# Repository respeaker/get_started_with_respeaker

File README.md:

## ReSpeaker Core V2 wiki

Now we have an new device, called **ReSpeaker Core V2**, with more powerful CPU, large eMMC and on-board 8channels microphone array.
Click here to [Getting started with ReSpeaker Core V2](/docs/ReSpeaker_Core_V2/README.md).

## ReSpeaker wiki

ReSpeaker is an open modular voice interface to hack things around you. Let you interact with your home appliances, your plant, your office, your internet-equipped devices or any other things in your daily life, all by your voice. Click here to [Getting Started with ReSpeaker](/docs/ReSpeaker/README.md).

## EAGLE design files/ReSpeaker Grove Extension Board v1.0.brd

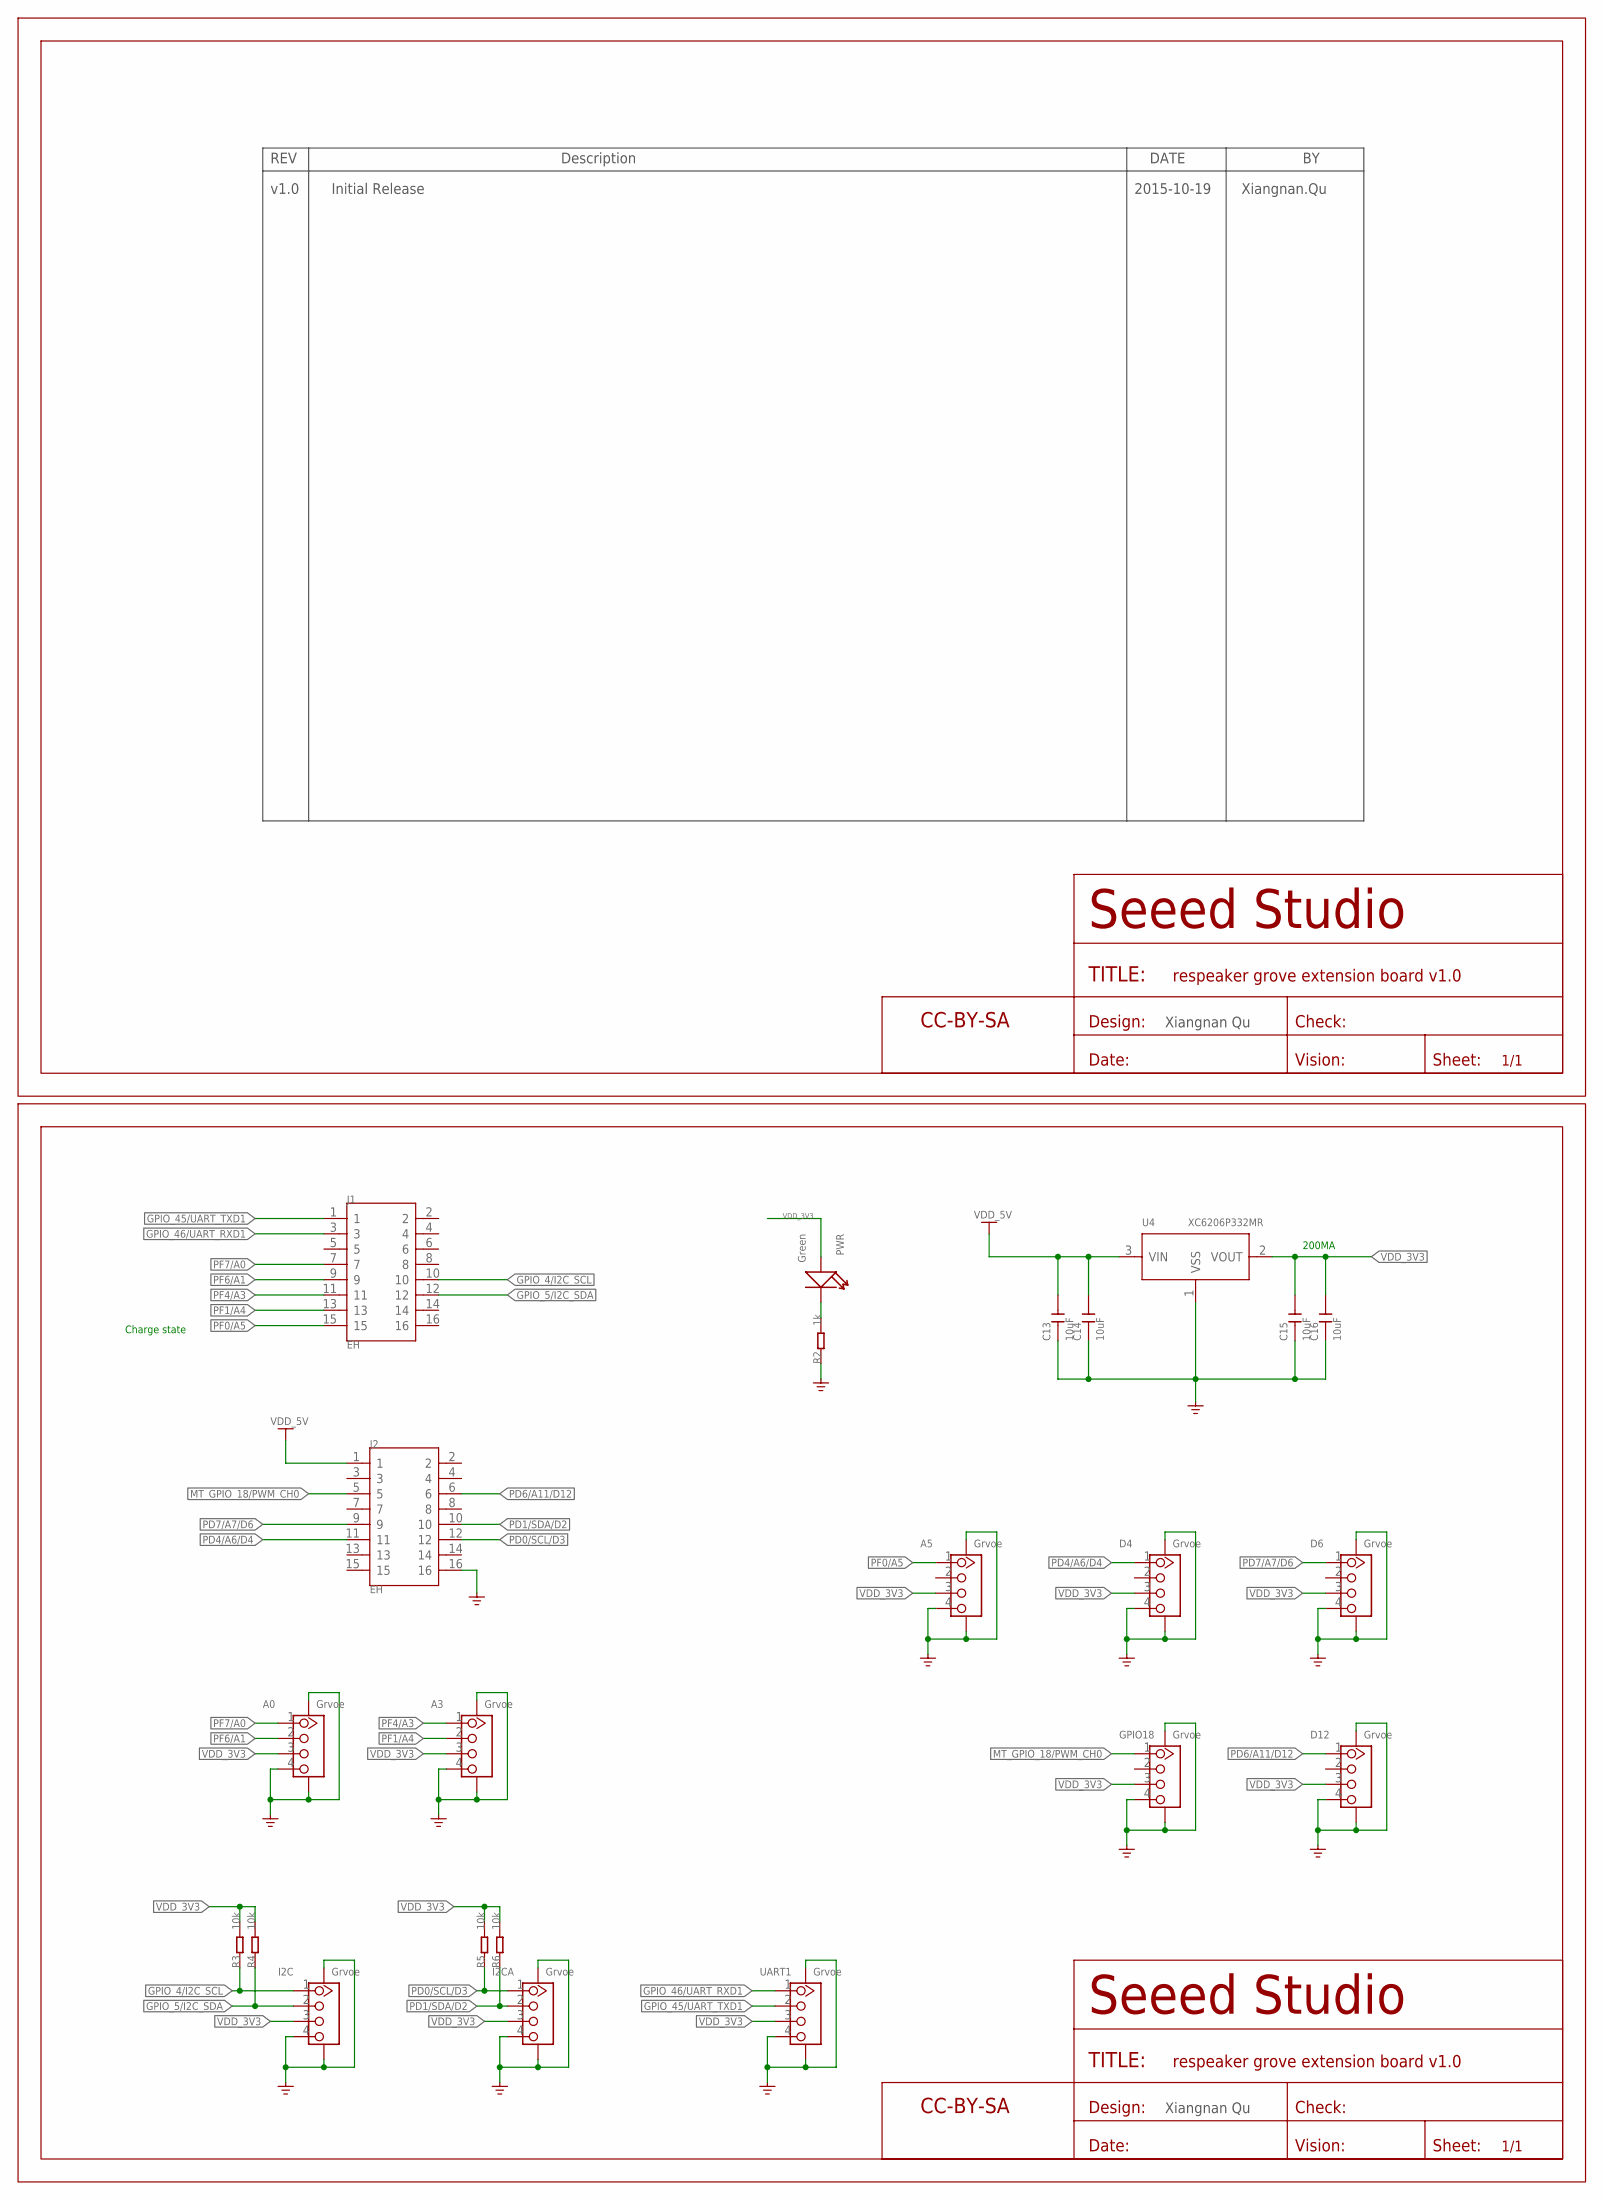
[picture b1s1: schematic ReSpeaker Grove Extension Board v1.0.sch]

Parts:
A0, A3, A5: Grvoe; HW4-SMD-2.0-90D
C13, C14, C15, C16: 10uF; C0603
D4, D6, D12: Grvoe; HW4-SMD-2.0-90D
FR1, FR2: SEEEDSTUDIO-OPEN-SCH-FRAME; SEEEDSTUDIO-PCB-FRAME
GPIO18: Grvoe; HW4-SMD-2.0-90D
I2C, I2CA: Grvoe; HW4-SMD-2.0-90D
J1, J2: EH; H2X8-2.0
PWR: Green; LED-0402
R2: 1k; R0402
R3, R4, R5, R6: 10k; R0402
U4: XC6206P332MR; SOT-23
UART1: Grvoe; HW4-SMD-2.0-90D

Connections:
GND: A0.4, A0.SS1, A0.SS2, A3.4, A3.SS1, A3.SS2, A5.4, A5.SS1, A5.SS2, C13.1, C14.1, C15.1, C16.1, D4.4, D4.SS1, D4.SS2, D6.4, D6.SS1, D6.SS2, D12.4, D12.SS1, D12.SS2, GPIO18.4, GPIO18.SS1, GPIO18.SS2, I2C.4, I2C.SS1, I2C.SS2, I2CA.4, I2CA.SS1, I2CA.SS2, J2.16, R2.1, U4.1 (VSS), UART1.4, UART1.SS1, UART1.SS2
GPIO_4/I2C_SCL: I2C.1, J1.10, R3.1
GPIO_5/I2C_SDA: I2C.2, J1.12, R4.1
GPIO_45/UART_TXD1: J1.1, UART1.2
GPIO_46/UART_RXD1: J1.3, UART1.1
MT_GPIO_18/PWM_CH0: GPIO18.1, J2.5
unnamed: PWR.-, R2.2
PD0/SCL/D3: I2CA.1, J2.12, R5.1
PD1/SDA/D2: I2CA.2, J2.10, R6.1
PD4/A6/D4: D4.1, J2.11
PD6/A11/D12: D12.1, J2.6
PD7/A7/D6: D6.1, J2.9
PF0/A5: A5.1, J1.15
PF1/A4: A3.2, J1.13
PF4/A3: A3.1, J1.11
PF6/A1: A0.2, J1.9
PF7/A0: A0.1, J1.7
VDD_3V3: A0.3, A3.3, A5.3, C15.2, C16.2, D4.3, D6.3, D12.3, GPIO18.3, I2C.3, I2CA.3, PWR.+, R3.2, R4.2, R5.2, R6.2, U4.2 (VOUT), UART1.3
VDD_5V: C13.2, C14.2, J2.1, U4.3 (VIN)

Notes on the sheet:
Xiangnan Qu
Charge state
200MA
Initial Release
v1.0
2015-10-19
Xiangnan.Qu

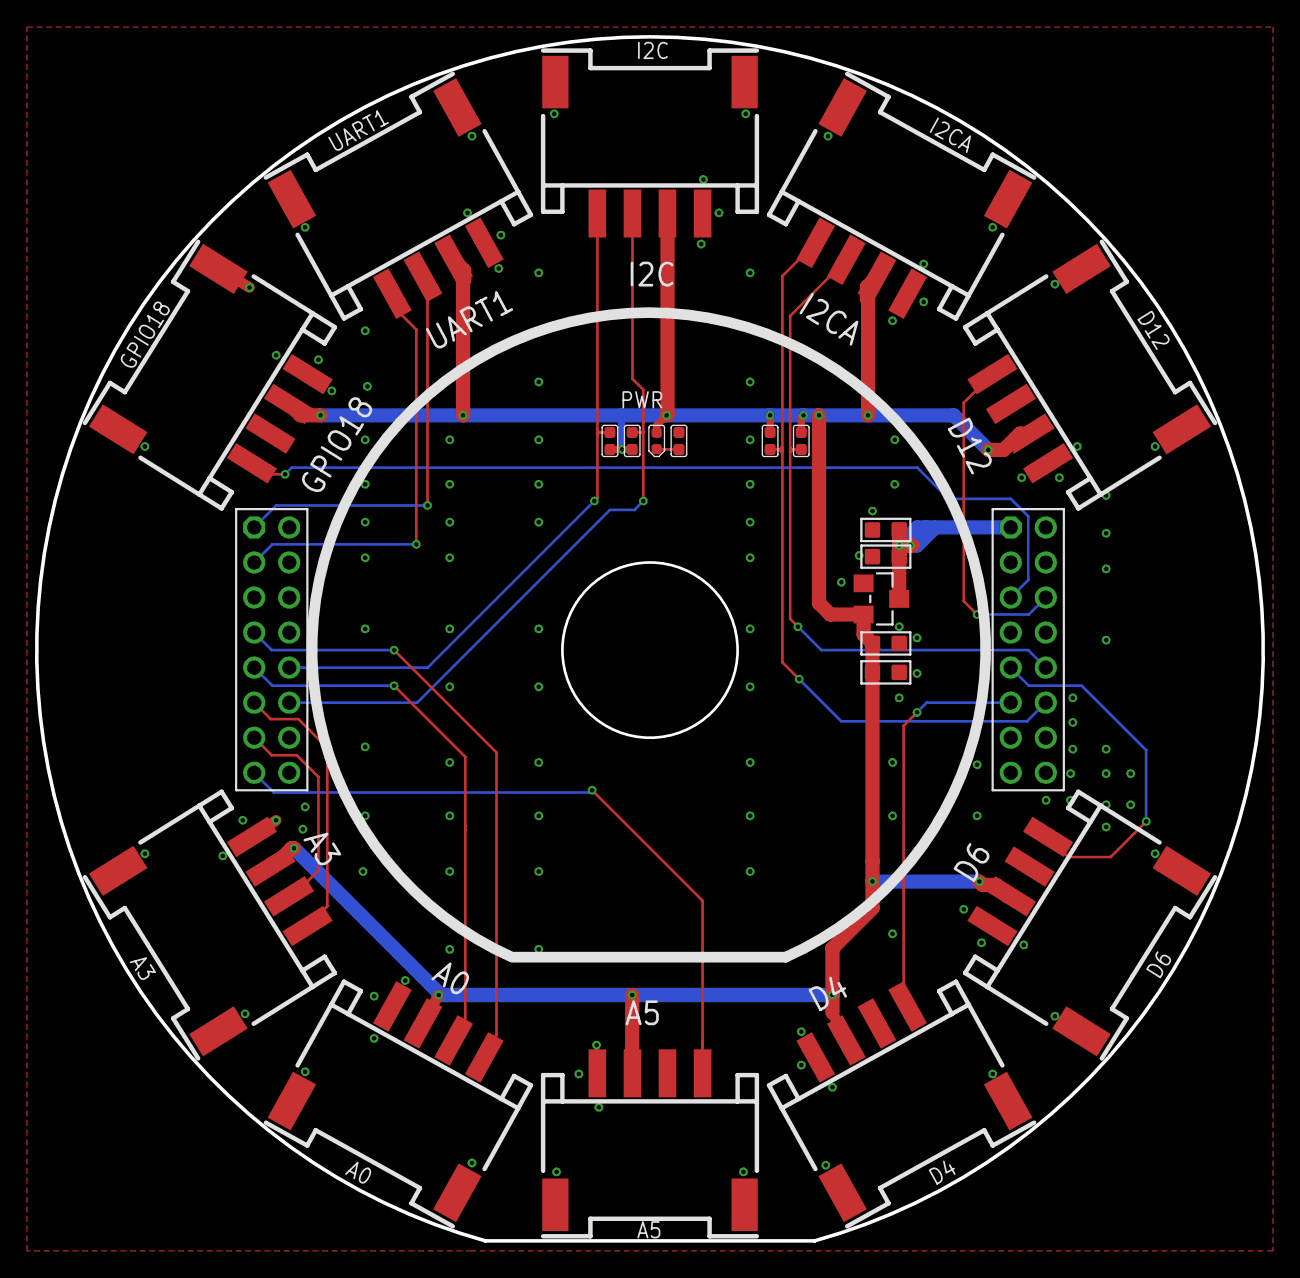
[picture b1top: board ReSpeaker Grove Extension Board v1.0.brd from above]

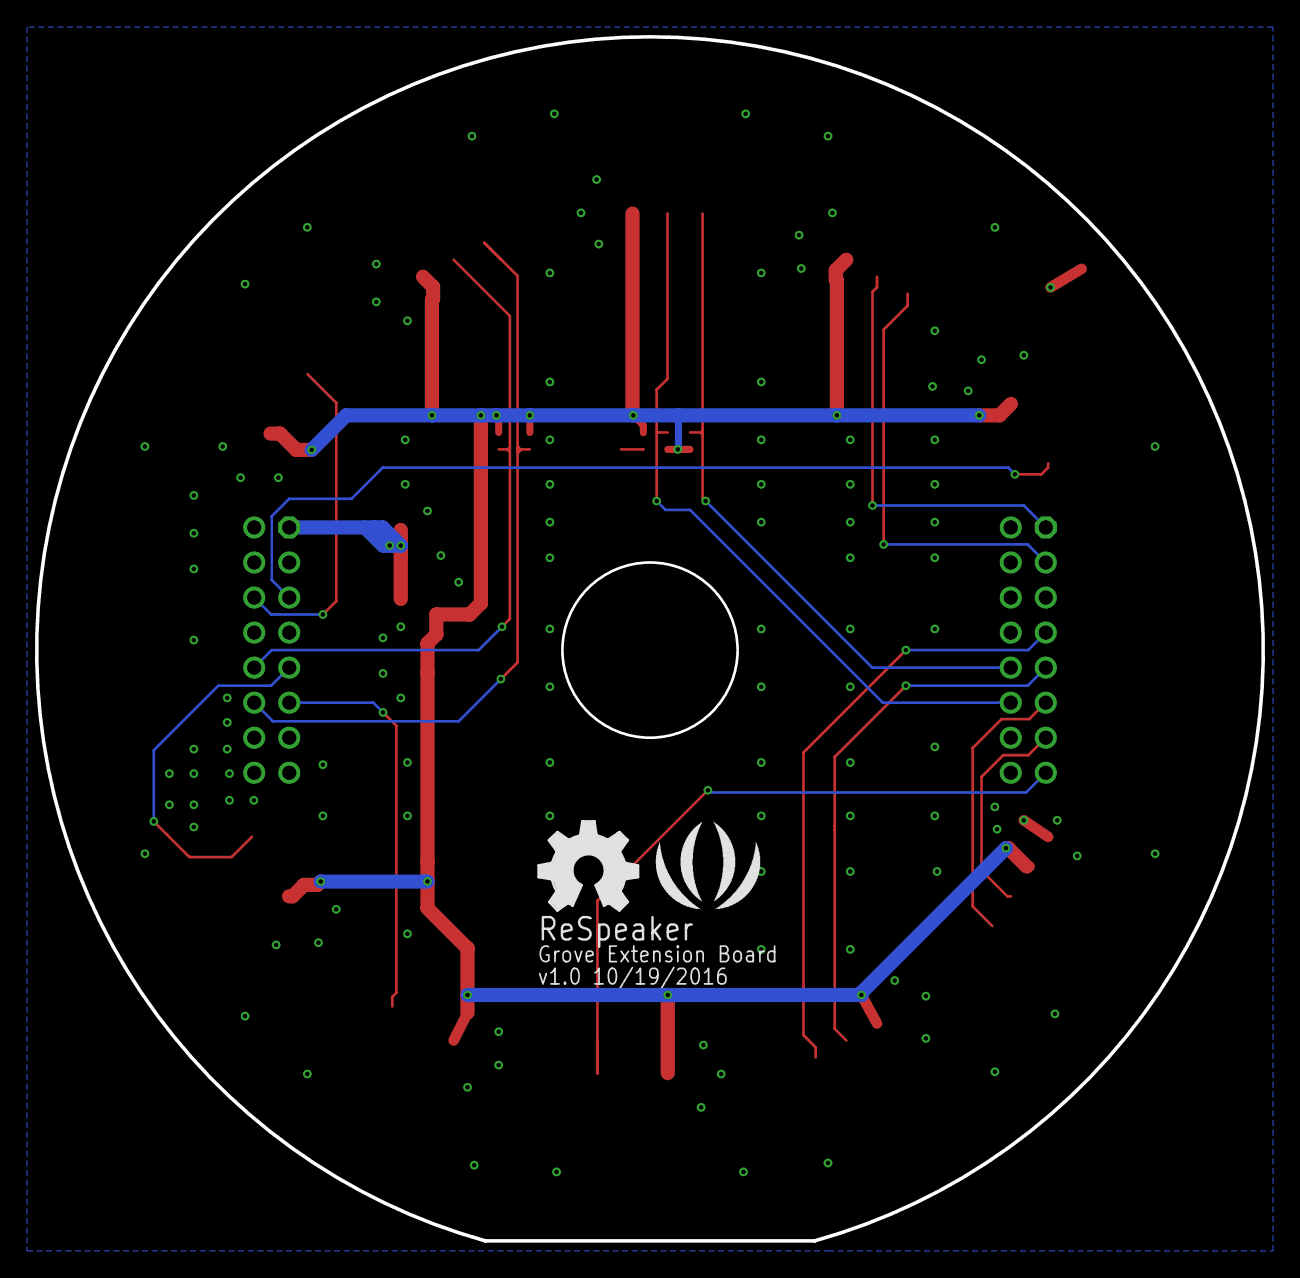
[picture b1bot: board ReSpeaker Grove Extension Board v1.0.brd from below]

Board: 2 copper layers, 70.0 x 68.7 mm, 27 parts (2 on the bottom side), 19 nets.

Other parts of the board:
U$75: OSHW_FILLX200_NOTEXT_TNAME
U$76: SEEED-SILK-TNAME-280*268MIL

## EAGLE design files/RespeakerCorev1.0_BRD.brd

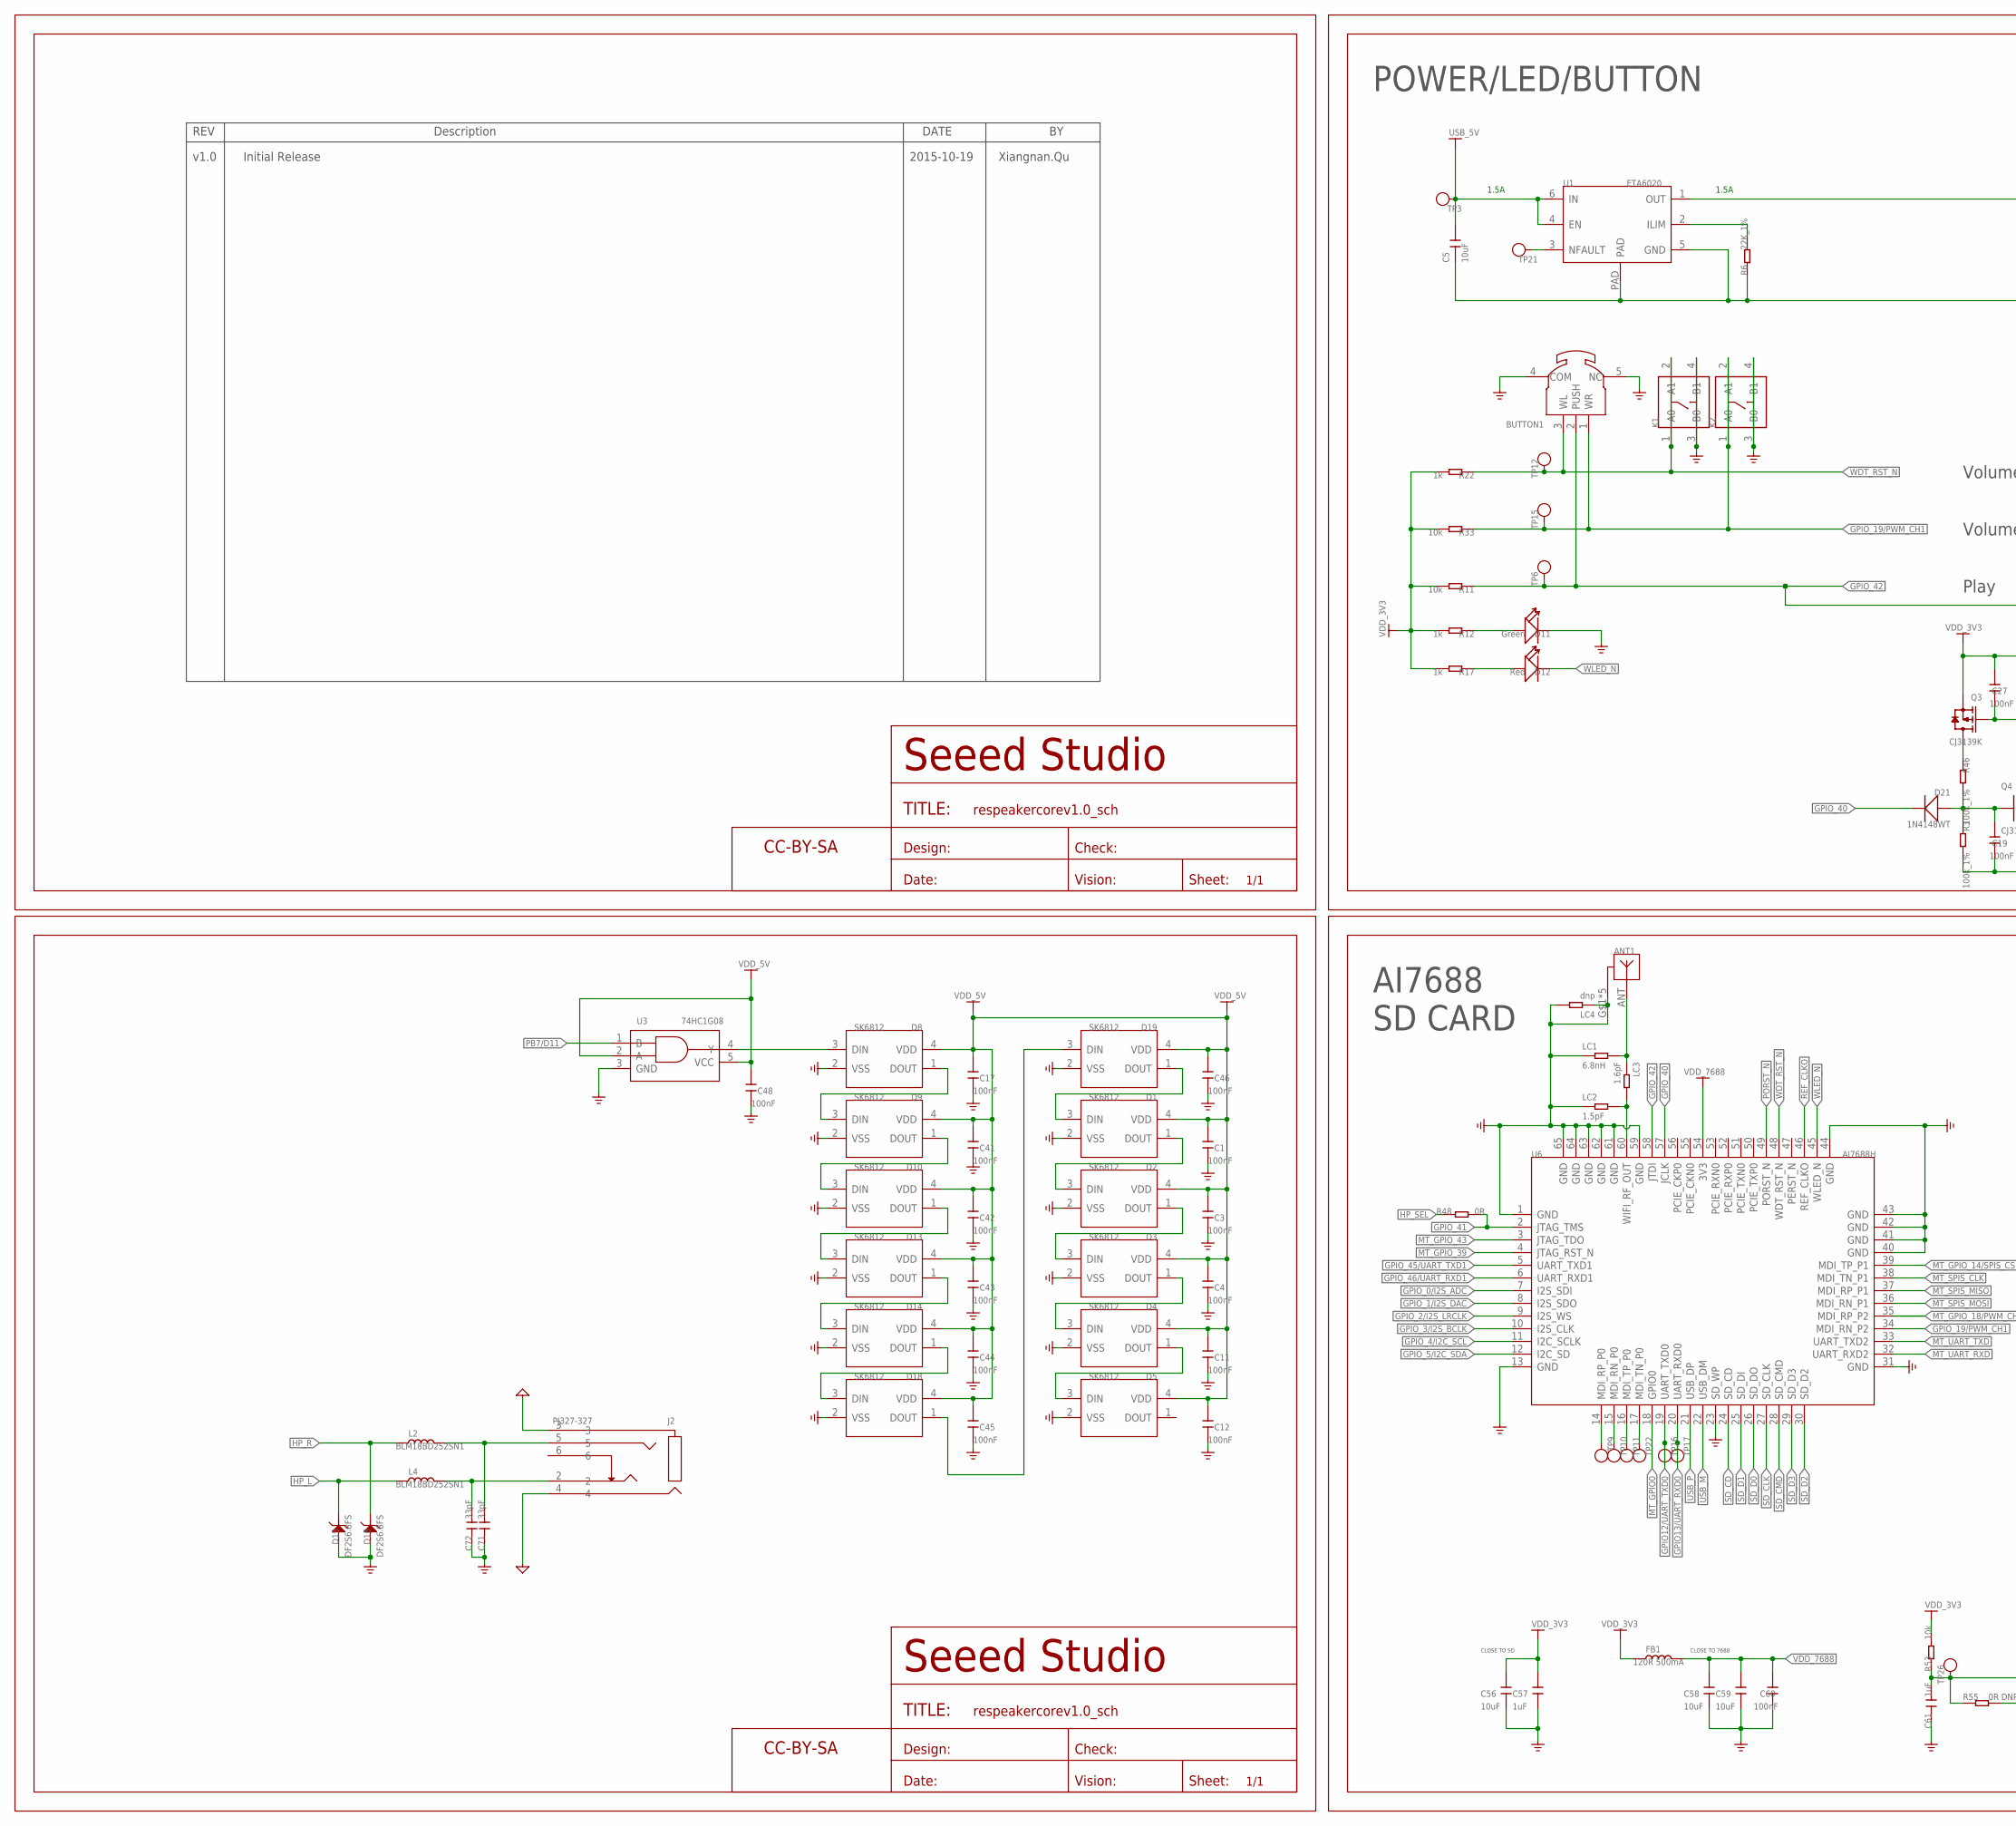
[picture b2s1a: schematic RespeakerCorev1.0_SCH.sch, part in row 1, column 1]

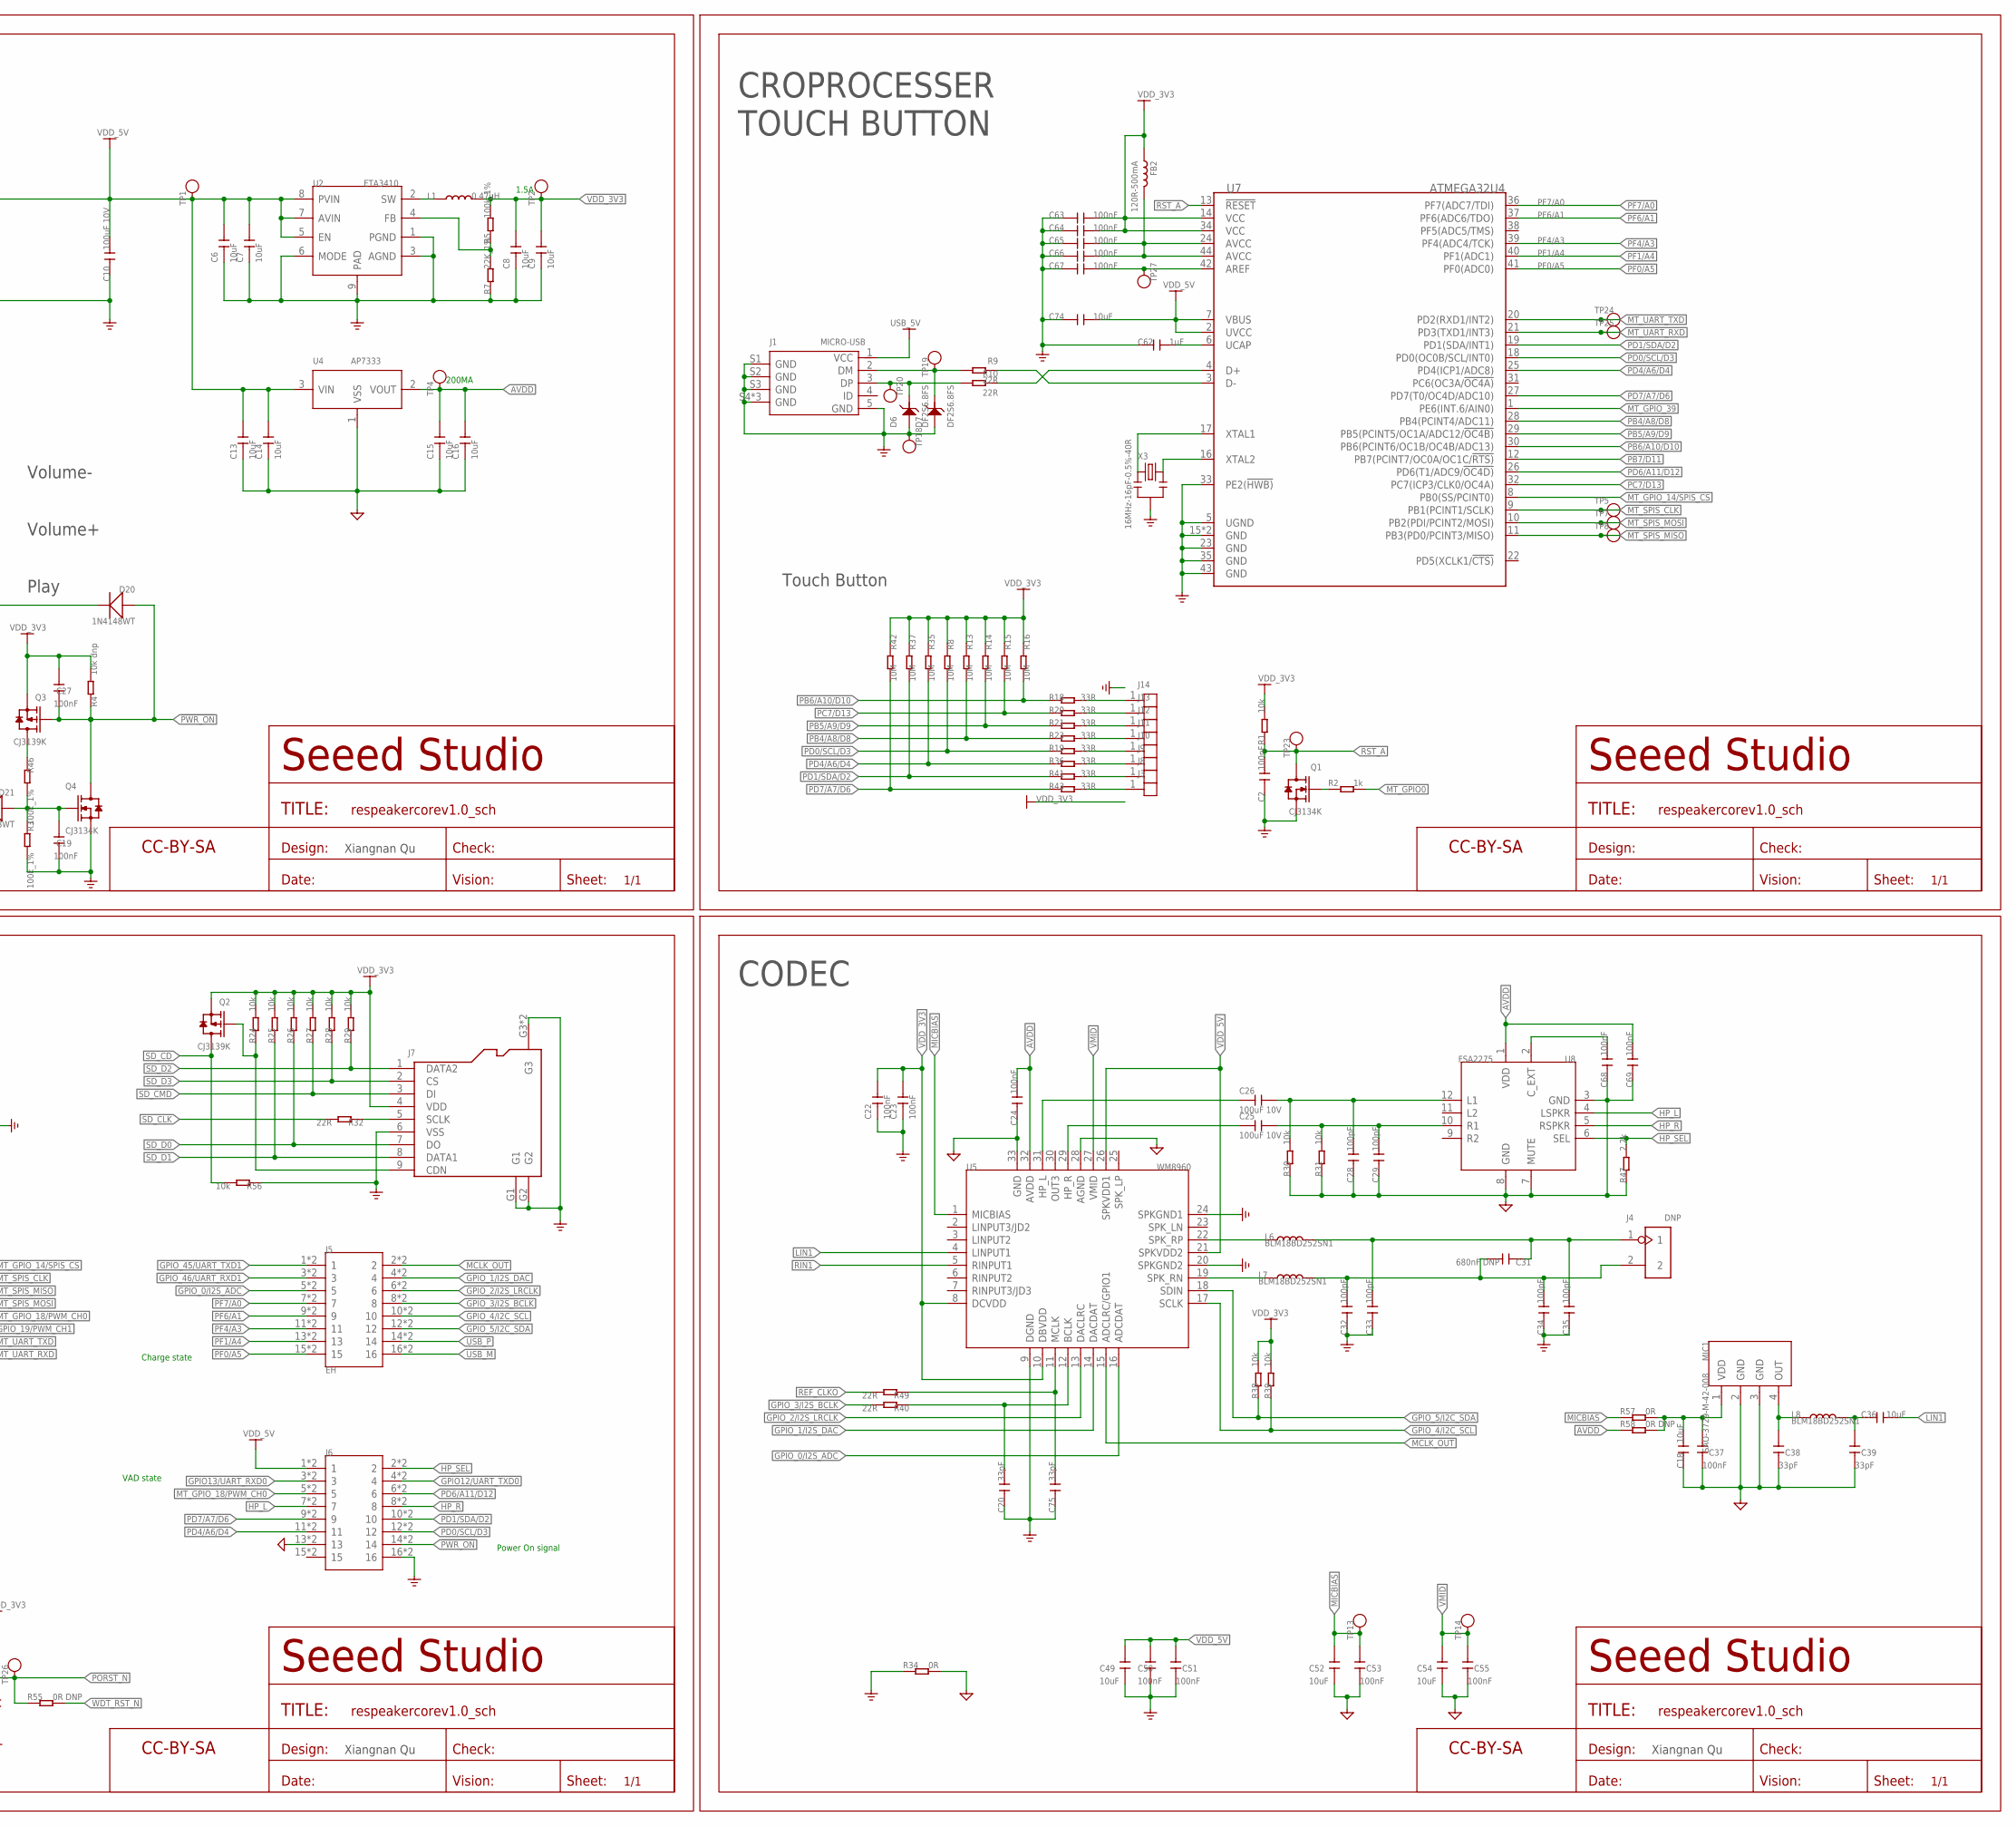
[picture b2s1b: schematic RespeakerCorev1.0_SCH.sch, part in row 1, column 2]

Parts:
ANT1: ANTENNA-ACA2012-BOTTOM; ANT2P-SMD-3.5X1.4MM-BOTTOM
BUTTON1: BUTTON3+2P; BUTTON3+2P-SMD-11.8X11.8X2.5MM
C1, C2, C3, C4, C11, C12, C17, C19, C22, C23, C24, C27, C37, C41, C42, C43, C44, C45, C46, C48, C50, C51, C53, C55, C60, C63, C64, C65, C66, C67, C68, C69: 100nF; C0402
C5, C6, C7, C8, C9, C13, C14, C15, C16, C18, C36, C49, C52, C54, C56, C58, C59, C74: 10uF; C0603
C10, C25, C26: 100uF 10V; C1206
C20, C38, C39, C71, C72, C75: 33pF; C0402
C28, C29, C32, C33, C34, C35: 100pF; C0402
C31: 680nF DNP; C0402
C57, C61, C62: 1uF; C0402
D1, D2, D3, D4, D5, D8, D9, D10, D13, D14, D18, D19: SK6812; LED4-SMD-3.5X3.7MM
D6, D7, D15, D16: DF2S6.8FS; SOD-923
D11: Green; LED-SIDE-VIEW-0603-RIGHT
D12: Red; LED-SIDE-VIEW-0603-RIGHT
D20, D21: 1N4148WT; SOD-523
FB1: 120R 500mA; L0603
FB2: 120R-500mA; L0603
FR1, FR2, FR3, FR4, FR5, FR7: SEEEDSTUDIO-OPEN-SCH-FRAME; SEEEDSTUDIO-PCB-FRAME
J1: MICRO-USB; MICRO-USB5+4P-SMD-0.65-B
J2: PJ327-327; AUDIO5P-14X5X4.4MM
J3, J8, J9, J10, J11, J12, J13, J14: HEADER-1P-3MM; 1P-DIP-6X4MM
J4: DNP; H2-2.54
J5: EH; H2X8-SMD_DRILL-2.0
J6: HEADER-2X8P-SMD_DRILL-2.0; H2X8-SMD_DRILL-2.0
J7: MICRO-SD-CARD-HOLDER-9P'MICROSD-9P'; MICRO-SD9+4P-SMD-16.1X14.5X1.85MM
K1, K2: BUTTON-4P-4.5X3.2; SW4P-SMD-4.5X3.2X2.5MM
L1: 0.47uH; L201610
L2, L4, L6, L7, L8: BLM18BD252SN1; L0603
LC1: 6.8nH; R0402
LC2: 1.5pF; R0402
LC3: 1.6pF; R0402
LC4: dnp; R0402
MIC1: SAO-3729-M-42-008; MIC4-SMD-3.76X2.95MM
Q1, Q4: CJ3134K; SOT-723
Q2, Q3: CJ3139K; SOT-723
R1, R11, R24, R25, R26, R27, R28, R29, R30, R31, R33, R38, R39, R53, R56: 10k; R0402
R2, R12, R17, R22: 1k; R0402
R3, R5, R46: 100k_1%; R0402
R4: 10k dnp; R0402
R6, R7: 22K_1%; R0402
R8, R13, R14, R15, R16, R35, R37, R42: 10M; R0402
R9, R10, R32, R40, R49: 22R; R0402
R18, R19, R20, R21, R23, R36, R41, R43: 33R; R0402
R34, R48, R57: 0R; R0402
R47: 2.2k; R0402
R55, R58: 0R DNP; R0402
TP1, TP2, TP3, TP4, TP5, TP6, TP7, TP8, TP12, TP13, TP14, TP15, TP16, TP17, TP18, TP19, TP20, TP21, TP23, TP24, TP25, TP26, TP27: TEST-POINT'4545'; TP-D45MIL
TP9, TP10, TP11, TP22: TEST-POINT'4080'; TP-80X40MIL
U1: ETA6020; DFN6G-0.65-2X2MM
U2: ETA3410; DFN8G-0.5-2X2MM
U3: 74HC1G08; SOT-353
U4: AP7333; SOT-23
U5: WM8960; QFN32G-0.5-5X5MM
U6: AI7688H; LGA65-1.7-24X32X1.8MM
U7: ATMEGA32U4; VQFN-44
U8: FSA2275; LEAD12P-SMD-0.4-1.8X1.8X0.5MM
X3: 16MHz-16pF-0.5%-40R; RESONATOR3-SMD-3.6X1.3X0.8MM

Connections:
!PWR_ON: C27.1, D20.+, J6.14, J6.P$14 (14), Q3.1 (G), Q4.3 (D), R4.1
AGND: C13.1, C14.1, C15.1, C16.1, C18.1, C24.1, C28.1, C29.1, C37.1, C38.1, C39.1, C52.2, C53.1, C54.2, C55.1, C68.1, C69.1, J2.3, J2.4, J6.13, J6.P$13 (13), MIC1.2 (GND), MIC1.3 (GND), R30.1, R31.1, R34.2, R47.1, U4.1 (VSS), U5.28 (AGND), U5.33 (GND), U8.3 (GND), U8.7 (MUTE), U8.8 (GND)
AVDD: C15.2, C16.2, C24.2, C69.2, R58.1, TP4.T, U4.2 (VOUT), U5.32 (AVDD), U8.1 (VDD)
GND: ANT1.G$1 (1), ANT1.G$2 (1), ANT1.G$4 (1), ANT1.GND1 (1), ANT1.GND2 (1), BUTTON1.4 (COM), BUTTON1.5 (NC), C1.1, C2.1, C3.1, C4.1, C5.1, C6.1, C7.1, C8.1, C9.1, C10.1, C11.1, C12.1, C17.1, C19.1, C20.1, C22.1, C23.1, C32.1, C33.1, C34.1, C35.1, C41.1, C42.1, C43.1, C44.1, C45.1, C46.1, C48.1, C49.2, C50.1, C51.1, C56.2, C57.2, C58.2, C59.2, C60.1, C61.1, C62.1, C63.1, C64.1, C65.1, C66.1, C67.1, C71.1, C72.1, C74.2, C75.1, D1.2 (VSS), D2.2 (VSS), D3.2 (VSS), D4.2 (VSS), D5.2 (VSS), D6.2 (1), D7.2 (1), D8.2 (VSS), D9.2 (VSS), D10.2 (VSS), D11.2 (-), D13.2 (VSS), D14.2 (VSS), D15.2 (1), D16.2 (1), D18.2 (VSS), D19.2 (VSS), J1.5 (GND), J1.S1 (GND), J1.S2 (GND), J1.S3 (GND), J1.S4 (GND), J1.S5 (GND), J1.S6 (GND), J6.16, J6.P$16 (16), J7.6 (VSS), J7.G1, J7.G2, J7.G3, J7.G4 (G3), K1.3 (B0), K1.4 (B1), K2.3 (B0), K2.4 (B1), LC1.1, LC2.1, LC4.1, LC4.2, Q1.2 (S), Q4.2 (S), R3.2, R6.1, R7.1, R34.1, R56.1, TP18.T, U1.5 (GND), U1.PAD, U2.1 (PGND), U2.3 (AGND), U2.6 (MODE), U2.9 (PAD), U3.3 (GND), U5.9 (DGND), U5.20 (SPKGND2), U5.24 (SPKGND1), U6.1 (GND), U6.13 (GND), U6.23 (SD_WP), U6.31 (GND), U6.40 (GND), U6.41 (GND), U6.42 (GND), U6.43 (GND), U6.44 (GND), U6.59 (GND), U6.61 (GND), U6.62 (GND), U6.63 (GND), U6.64 (GND), U6.65 (GND), U7.5 (UGND)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
GPIO12/UART_TXD0: J6.4, J6.P$4 (4), TP16.T, U6.19 (UART_TXD0)
GPIO13/UART_RXD0: J6.3, J6.P$3 (3), TP17.T, U6.20 (UART_RXD0)
GPIO_0/I2S_ADC: J5.5, J5.P$5 (5), U5.16 (ADCDAT), U6.7 (I2S_SDI)
GPIO_1/I2S_DAC: J5.4, J5.P$4 (4), U5.14 (DACDAT), U6.8 (I2S_SDO)
GPIO_2/I2S_LRCLK: J5.6, J5.P$6 (6), U5.13 (DACLRC), U6.9 (I2S_WS)
GPIO_3/I2S_BCLK: J5.8, J5.P$8 (8), R40.2, U6.10 (I2S_CLK)
GPIO_4/I2C_SCL: J5.10, J5.P$10 (10), R39.1, U5.17 (SCLK), U6.11 (I2C_SCLK)
GPIO_5/I2C_SDA: J5.12, J5.P$12 (12), R38.1, U5.18 (SDIN), U6.12 (I2C_SD)
GPIO_19/PWM_CH1: BUTTON1.1 (WR), K2.1 (A0), K2.2 (A1), R33.1, TP15.T, U6.34 (MDI_RN_P2)
GPIO_40: D21.-, U6.57 (JCLK)
GPIO_41: R48.1, U6.2 (JTAG_TMS)
GPIO_42: BUTTON1.2 (PUSH), D20.-, R11.1, TP6.T, U6.58 (JTDI)
GPIO_45/UART_TXD1: J5.1, J5.P$1 (1), U6.5 (UART_TXD1)
GPIO_46/UART_RXD1: J5.3, J5.P$3 (3), U6.6 (UART_RXD1)
HP_L: D15.1 (2), J6.7, J6.P$7 (7), L4.1, U8.4 (LSPKR)
HP_R: D16.1 (2), J6.8, J6.P$8 (8), L2.1, U8.5 (RSPKR)
HP_SEL: J6.2, J6.P$2 (2), R47.2, R48.2, U8.6 (SEL)
LIN1: C36.2, U5.4 (LINPUT1)
MCLK_OUT: J5.2, J5.P$2 (2), U5.15 (ADCLRC/GPIO1)
MICBIAS: C52.1, C53.2, R57.1, TP13.T, U5.1 (MICBIAS)
MIC_VDD: C18.2, C37.2, MIC1.1 (VDD), R57.2, R58.2
MT_GPIO0: R2.2, U6.18 (GPIO0)
MT_GPIO_14/SPIS_CS: U6.39 (MDI_TP_P1), U7.8 (PB0(SS/PCINT0))
MT_GPIO_18/PWM_CH0: J6.5, J6.P$5 (5), U6.35 (MDI_RP_P2)
MT_GPIO_39: U6.4 (JTAG_RST_N), U7.1 (PE6(INT.6/AIN0))
MT_GPIO_43: U6.3 (JTAG_TDO)
MT_SPIS_CLK: TP5.T, U6.38 (MDI_TN_P1), U7.9 (PB1(PCINT1/SCLK))
MT_SPIS_MISO: TP8.T, U6.37 (MDI_RP_P1), U7.11 (PB3(PD0/PCINT3/MISO))
MT_SPIS_MOSI: TP7.T, U6.36 (MDI_RN_P1), U7.10 (PB2(PDI/PCINT2/MOSI))
MT_UART_RXD: TP25.T, U6.32 (UART_RXD2), U7.21 (PD3(TXD1/INT3))
MT_UART_TXD: TP24.T, U6.33 (UART_TXD2), U7.20 (PD2(RXD1/INT2))
unnamed: Q3.3 (D), R46.1
unnamed: LC2.2, LC3.2, U6.60 (WIFI_RF_OUT)
unnamed: D11.1 (+), R12.1
unnamed: C68.2, U8.2 (C_EXT)
unnamed: C75.2, R49.1, U5.11 (MCLK)
unnamed: C38.2, L8.1, MIC1.4 (OUT)
unnamed: D12.1 (+), R17.1
unnamed: R10.1, U7.4 (D+)
unnamed: J7.5 (SCLK), R32.1
unnamed: R9.1, U7.3 (D-)
unnamed: D9.1 (DOUT), D10.3 (DIN)
unnamed: R6.2, U1.2 (ILIM)
unnamed: D1.3 (DIN), D19.1 (DOUT)
unnamed: L6.1, U5.22 (SPK_RP)
unnamed: D7.1 (2), J1.2 (DM), R9.2, TP19.T
unnamed: D6.1 (2), J1.3 (DP), R10.2, TP20.T
unnamed: D10.1 (DOUT), D13.3 (DIN)
unnamed: D8.1 (DOUT), D9.3 (DIN)
unnamed: J13.1, R20.2
unnamed: C19.2, D21.+, Q4.1 (G), R3.1, R46.2
unnamed: J14.1, R18.2
unnamed: D13.1 (DOUT), D14.3 (DIN)
unnamed: C36.1, C39.2, L8.2
unnamed: D14.1 (DOUT), D18.3 (DIN)
unnamed: C20.2, R40.1, U5.12 (BCLK)
unnamed: TP9.1, U6.14 (MDI_RP_P0)
unnamed: Q1.1 (G), R2.1
unnamed: L1.1, U2.2 (SW)
unnamed: D18.1 (DOUT), D19.3 (DIN)
unnamed: J8.1, R41.2
unnamed: R5.1, R7.2, U2.4 (FB)
unnamed: J12.1, R21.2
unnamed: J11.1, R23.2
unnamed: J3.1, R43.2
unnamed: J9.1, R36.2
unnamed: J10.1, R19.2
unnamed: L7.1, U5.19 (SPK_RN)
unnamed: C31.1, C33.2, C35.2, J4.1, L6.2
unnamed: C62.2, U7.6 (UCAP)
unnamed: C67.2, TP27.T, U7.42 (AREF)
unnamed: D1.1 (DOUT), D2.3 (DIN)
unnamed: C65.2, C66.2, FB2.2, U7.24 (AVCC), U7.44 (AVCC)
unnamed: D2.1 (DOUT), D3.3 (DIN)
unnamed: D3.1 (DOUT), D4.3 (DIN)
unnamed: D4.1 (DOUT), D5.3 (DIN)
unnamed: C31.2, C32.2, C34.2, J4.2, L7.2
unnamed: U7.17 (XTAL1), X3.1
unnamed: U7.16 (XTAL2), X3.3
unnamed: ANT1.ANT, LC1.2, LC3.1
unnamed: TP10.1, U6.15 (MDI_RN_P0)
unnamed: TP11.1, U6.16 (MDI_TP_P0)
unnamed: TP22.1, U6.17 (MDI_TN_P0)
unnamed: C26.2, C28.2, R30.2, U8.12 (L1)
unnamed: C25.1, U5.29 (HP_R)
unnamed: D8.3 (DIN), U3.4 (Y)
unnamed: C26.1, U5.31 (HP_L)
unnamed: C25.2, C29.2, R31.2, U8.10 (R1)
unnamed: C72.2, J2.2, L4.2
unnamed: C71.2, J2.5, L2.2
PB4/A8/D8: R13.1, R23.1, U7.28 (PB4(PCINT4/ADC11))
PB5/A9/D9: R14.1, R21.1, U7.29 (PB5(PCINT5/OC1A/ADC12/!OC4B))
PB6/A10/D10: R16.1, R18.1, U7.30 (PB6(PCINT6/OC1B/OC4B/ADC13))
PB7/D11: U3.1 (B), U7.12 (PB7(PCINT7/OC0A/OC1C/!RTS))
PC7/D13: R15.1, R20.1, U7.32 (PC7(ICP3/CLK0/OC4A))
PD0/SCL/D3: J6.12, J6.P$12 (12), R8.1, R19.1, U7.18 (PD0(OC0B/SCL/INT0))
PD1/SDA/D2: J6.10, J6.P$10 (10), R37.1, R41.1, U7.19 (PD1(SDA/INT1))
PD4/A6/D4: J6.11, J6.P$11 (11), R35.1, R36.1, U7.25 (PD4(ICP1/ADC8))
PD6/A11/D12: J6.6, J6.P$6 (6), U7.26 (PD6(T1/ADC9/!OC4D))
PD7/A7/D6: J6.9, J6.P$9 (9), R42.1, R43.1, U7.27 (PD7(T0/OC4D/ADC10))
PF0/A5: J5.15, J5.P$15 (15), U7.41 (PF0(ADC0))
PF1/A4: J5.13, J5.P$13 (13), U7.40 (PF1(ADC1))
PF4/A3: J5.11, J5.P$11 (11), U7.39 (PF4(ADC4/TCK))
PF6/A1: J5.9, J5.P$9 (9), U7.37 (PF6(ADC6/TDO))
PF7/A0: J5.7, J5.P$7 (7), U7.36 (PF7(ADC7/TDI))
PORST_N: C61.2, R53.1, R55.1, TP26.T, U6.49 (PORST_N)
PW_FAULT: TP21.T, U1.3 (NFAULT)
REF_CLKO: R49.2, U6.46 (REF_CLKO)
RIN1: U5.5 (RINPUT1)
RST_A: C2.2, Q1.3 (D), R1.1, TP23.T, U7.13 (!RESET)
SD_CD: Q2.3 (D), R56.2, U6.24 (SD_CD)
SD_CLK: R32.2, U6.27 (SD_CLK)
SD_CMD: J7.3 (DI), R27.1, U6.28 (SD_CMD)
SD_D0: J7.7 (DO), R26.1, U6.26 (SD_DO)
SD_D1: J7.8 (DATA1), R25.1, U6.25 (SD_DI)
SD_D2: J7.1 (DATA2), R29.1, U6.30 (SD_D2)
SD_D3: J7.2 (CS), R28.1, U6.29 (SD_D3)
SSSS: J7.9 (CDN), Q2.1 (G), R24.1
USB_5V: C5.2, J1.1 (VCC), TP3.T, U1.4 (EN), U1.6 (IN)
USB_M: J5.16, J5.P$16 (16), U6.22 (USB_DM)
USB_P: J5.14, J5.P$14 (14), U6.21 (USB_DP)
VDD_3V3: C8.2, C9.2, C22.2, C23.2, C27.2, C56.1, C57.1, C63.2, C64.2, FB1.1, FB2.1, J7.4 (VDD), L1.2, Q2.2 (S), Q3.2 (S), R1.2, R4.2, R5.2, R8.2, R11.2, R12.2, R13.2, R14.2, R15.2, R16.2, R17.2, R22.2, R24.2, R25.2, R26.2, R27.2, R28.2, R29.2, R33.2, R35.2, R37.2, R38.2, R39.2, R42.2, R53.2, TP2.T, U5.8 (DCVDD), U5.10 (DBVDD), U7.14 (VCC), U7.34 (VCC)
VDD_5V: C1.2, C3.2, C4.2, C6.2, C7.2, C10.2, C11.2, C12.2, C13.2, C14.2, C17.2, C41.2, C42.2, C43.2, C44.2, C45.2, C46.2, C48.2, C49.1, C50.2, C51.2, C74.1, D1.4 (VDD), D2.4 (VDD), D3.4 (VDD), D4.4 (VDD), D5.4 (VDD), D8.4 (VDD), D9.4 (VDD), D10.4 (VDD), D13.4 (VDD), D14.4 (VDD), D18.4 (VDD), D19.4 (VDD), J6.1, J6.P$1 (1), TP1.T, U1.1 (OUT), U2.5 (EN), U2.7 (AVIN), U2.8 (PVIN), U3.2 (A), U3.5 (VCC), U4.3 (VIN), U5.21 (SPKVDD2), U5.26 (SPKVDD1), U7.2 (UVCC), U7.7 (VBUS)
VDD_7688: C58.1, C59.1, C60.2, FB1.2, U6.54 (3V3)
VMID: C54.1, C55.2, TP14.T, U5.27 (VMID)
WDT_RST_N: BUTTON1.3 (WL), K1.1 (A0), K1.2 (A1), R22.1, R55.2, TP12.T, U6.48 (WDT_RST_N)
WLED_N: D12.2 (-), U6.45 (WLED_N)

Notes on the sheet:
Xiangnan Qu
POWER/LED/BUTTON
AI7688 SD CARD
CODEC
CLOSE TO SD
CLOSE TO 7688
CROPROCESSER TOUCH BUTTON
1.5A
200MA
Touch Button
Play
Volume+
Volume-
Power On signal
Charge state
VAD state
Initial Release
v1.0
2015-10-19
Xiangnan.Qu

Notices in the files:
parts and their libraries:
moudle-new: This work is licensed under the Creative Commons Attribution 4.0 International License.
To view a copy of this license,visit:
http://creativecommons.org/licenses/by-sa/4.0
moudle-new: CC-BY-SA
